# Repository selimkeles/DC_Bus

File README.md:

# DC Bus

Single-phase 230 V AC, 50 Hz input rectified to a 320 V DC bus.

## Features

- 230 V AC / 50 Hz single-phase input
- 320 V DC bus
- Bulk capacitors rated for 5 A current ripple with less than 20 V ripple at 50 Hz
- Precharge circuit to limit inrush current
- Bleeder resistor to discharge the bulk capacitors in under 5 minutes after power-off

## Board

## Schematic

The generated PDF is available at [output/schematic.pdf](output/schematic.pdf).

## Project Files

- `DCBus.kicad_pro` - KiCad project
- `DCBus.kicad_sch` - schematic
- `DCBus.kicad_pcb` - PCB layout
- `output/` - generated board/schematic images, schematic PDF, and check reports
- `output/erc.json`, `output/drc.json` - ERC and DRC reports
- `bom/ibom.html` - interactive bill of materials

## Design Checks

Reports: [ERC JSON](output/erc.json) and [DRC JSON](output/drc.json).

## Generation

Board render:

```sh
kicad-cli pcb render --output output/board.png --rotate '-45,0,135' --width 1920 --height 1080 DCBus.kicad_pcb
```

Schematic PDF:

```sh
kicad-cli sch export pdf -o output/schematic.pdf DCBus.kicad_sch
```

Gerbers and drill files:

```sh
mkdir -p build/gerbers
kicad-cli pcb export gerbers --layers F.Cu,B.Cu,F.Paste,B.Paste,F.Silkscreen,B.Silkscreen,F.Mask,B.Mask,Edge.Cuts -o build/gerbers DCBus.kicad_pcb
kicad-cli pcb export drill --generate-report --report-path build/gerbers/DCBus-drill.rpt -o build/gerbers DCBus.kicad_pcb
cd build/gerbers && python3 -m zipfile -c ../DCBus-gerbers.zip *
```

Design checks:

```sh
kicad-cli sch erc --format json --severity-all -o output/erc.json DCBus.kicad_sch
kicad-cli pcb drc --format json --severity-all -o output/drc.json DCBus.kicad_pcb
```

BOM:

```sh
kicad-cli sch export bom --group-by "Footprint" --fields "Reference,Value,Footprint,QUANTITY,DNP,Datasheet" -o output/bom.csv DCBus.kicad_sch
```

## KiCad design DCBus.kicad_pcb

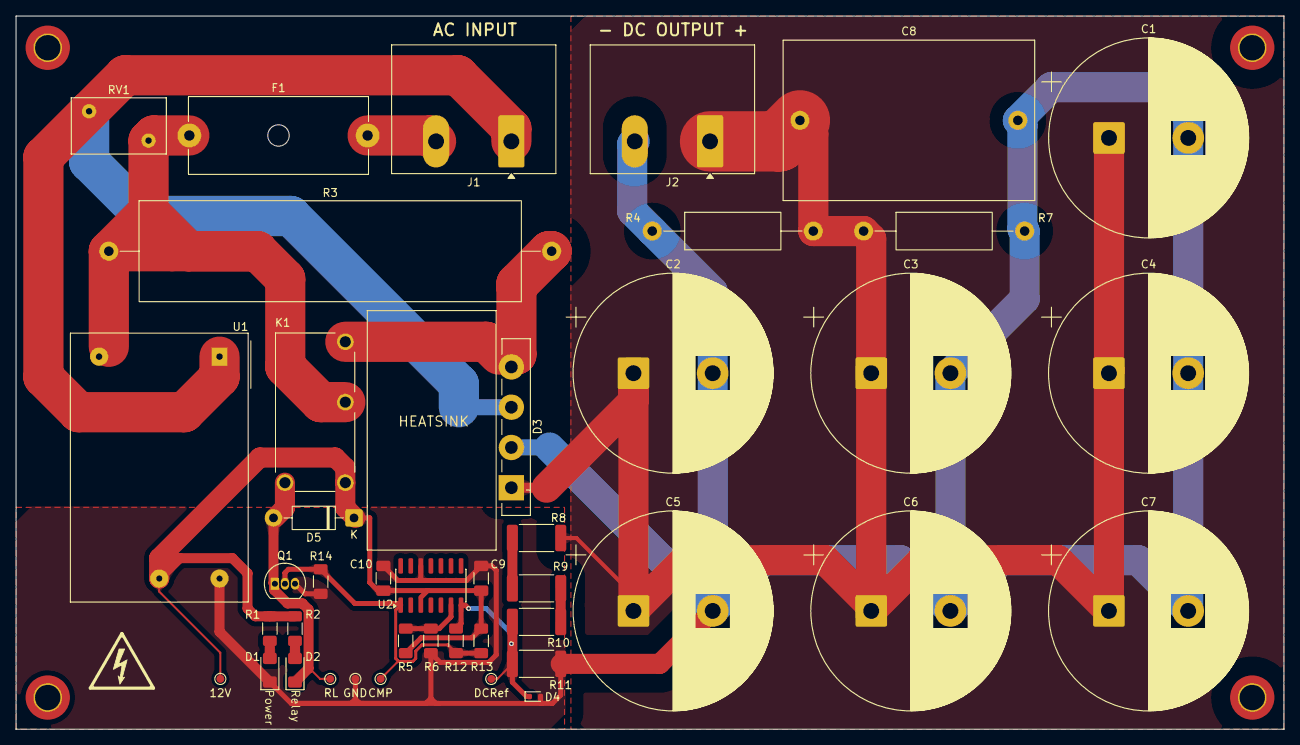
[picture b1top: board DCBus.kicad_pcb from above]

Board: 2 copper layers, 160.0 x 90.0 mm, 42 parts (0 on the bottom side), 15 nets.

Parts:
12V: TestPoint; TestPoint_Pad_D1.0mm
C1, C2, C3, C4, C5, C6, C7: 470u; CP_Radial_D25.0mm_P10.00mm_SnapIn
C8: 10u; C_Rect_L31.5mm_W20.0mm_P27.50mm_MKS4
C9: 100n; C_1206_3216Metric_Pad1.33x1.80mm_HandSolder
C10: 10uF; C_1206_3216Metric_Pad1.33x1.80mm_HandSolder
CMP: TestPoint; TestPoint_Pad_D1.0mm
D1, D2: LED; LED_1206_3216Metric_Pad1.42x1.75mm_HandSolder
D3: GBU3510; Diode_Bridge_Vishay_GBU
D4: 9.1V; D_SOD-523
D5: 1N4007; D_DO-41_SOD81_P10.16mm_Horizontal
DCRef: TestPoint; TestPoint_Pad_D1.0mm
F1: 10A Fuse; Fuseholder_Cylinder-5x20mm_Schurter_0031_8201_Horizontal_Op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
GND: TestPoint; TestPoint_Pad_D1.0mm
J1: AC_IN_TERM; TerminalBlock_Ningbo-Kagnex_HB9500M_1x02_P9.5mm
J2: DC_OUT_TERM; TerminalBlock_Ningbo-Kagnex_HB9500M_1x02_P9.5mm
K1: ALQ312; RELAY_ALQ312
Q1: BC547; TO-92_Inline
R1, R2: 1K; R_1206_3216Metric_Pad1.30x1.75mm_HandSolder
R3: 100R 10W; R_Axial_Power_L48.0mm_W12.5mm_P55.88mm
R4, R7: 100K; R_Axial_DIN0414_L11.9mm_D4.5mm_P20.32mm_Horizontal
R5, R6: 33K; R_1206_3216Metric_Pad1.30x1.75mm_HandSolder
R8, R9: 270K; R_2512_6332Metric_Pad1.40x3.35mm_HandSolder
R10: 20K; R_2512_6332Metric_Pad1.40x3.35mm_HandSolder
R11: 12K; R_2512_6332Metric_Pad1.40x3.35mm_HandSolder
R12: 120K; R_1206_3216Metric_Pad1.30x1.75mm_HandSolder
R13, R14: 10K; R_1206_3216Metric_Pad1.30x1.75mm_HandSolder
RL: TestPoint; TestPoint_Pad_D1.0mm
RV1: Varistor 275VAC; RV_Disc_D12mm_W7.1mm_P7.5mm
U1: IRM-02-12; Converter_ACDC_MeanWell_IRM-02-xx_THT
U2: LM339; SOIC-14_3.9x8.7mm_P1.27mm

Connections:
+12V: 12V.1 (1_1), C9.1, C10.1, D5.1 (K), K1.C1, R1.1, R2.1, R5.2, R13.2, U1.4 (+Vo), U2.3 (V+)
+VDC: C1.1, C2.1, C3.1, C4.1, C5.1, C6.1, C7.1, C8.1, D3.1 (+), J2.1, R4.2, R7.1, R8.2
/Bus_Ref: D4.1 (K), DCRef.1 (1_1), R10.1, R11.2, R12.2, U2.7 (+)
/Comp_Output: CMP.1 (1_1), Q1.2 (B), R12.1, R13.1, R14.2, U2.1
/LINE_F: F1.1, K1.COM, R3.1, RV1.1, U1.2 (AC/L)
/LINE_SW: D3.4, K1.NO, R3.2
/Relay Status: D2.1 (K), D5.2 (A), K1.C2, Q1.1 (C), RL.1 (1_1)
GND: C1.2, C2.2, C3.2, C4.2, C5.2, C6.2, C7.2, C8.2, C9.2, C10.2, D1.1 (K), D3.2 (-), D4.2 (A), GND.1 (1_1), J2.2, Q1.3 (E), R4.1, R6.1, R7.2, R11.1, R14.1, U1.3 (-Vo), U2.12 (V-)
LINE: F1.2, J1.2
NEUT: D3.3, J1.1, RV1.2, U1.1 (AC/N)
unnamed: D1.2 (A), R1.2
unnamed: D2.2 (A), R2.2
unnamed: R8.1, R9.2
unnamed: R9.1, R10.2
unnamed: R5.1, R6.2, U2.6 (-)
